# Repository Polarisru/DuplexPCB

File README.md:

# DuplexPCB

This KiCad action plugin tries to create the second part of the duplex PCB.<br>

## Install
Just copy the teardrop folder into the KiCad plugins directory, then restart KiCad. The DuplexPCB plugin should now be available in the Tools/External plugin menu.

## Usage
To duplicate existing PCB you need to create a mapping file first. It must be a simple text file with mapping for all components you want to duplicate.

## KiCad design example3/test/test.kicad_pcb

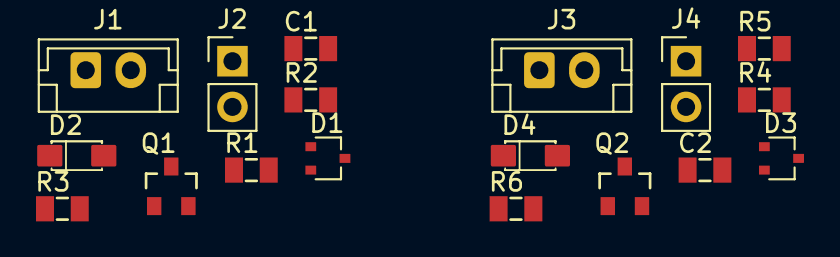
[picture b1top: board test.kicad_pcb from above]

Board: 2 copper layers, 18 parts (0 on the bottom side), 13 nets, no tracks yet.

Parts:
C1, C2: C0805
D1, D3: BAT54SW; SOT-323_SC-70
D2, D4: SMF30A; D_SOD-123FL
J1, J3: Conn_JST_B2B_EH_01x02; JST_EH_B2B-EH-A_1x02_P2.50mm_Vertical
J2, J4: PinHeader_1x02_P2.54mm_Vertical
Q1, Q2: DMN3023L; SOT23-3
R1, R2, R3, R4, R5, R6: R0805

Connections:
GND: C1.2, C2.2, D2.2, D4.2, J1.2, J2.2, J3.2, J4.2, R2.1, R5.1
unnamed: C1.1, D2.1, Q1.1, R3.1
unnamed: C2.1, D4.1, Q2.1, R6.1
unnamed: D1.1, R1.1
unnamed: D1.2, R3.2
unnamed: D1.3, R2.2
unnamed: D3.1, R4.1
unnamed: D3.2, R6.2
unnamed: D3.3, R5.2
unnamed: J1.1, Q1.3, R1.2
unnamed: J2.1, Q1.2
unnamed: J3.1, Q2.3, R4.2
unnamed: J4.1, Q2.2

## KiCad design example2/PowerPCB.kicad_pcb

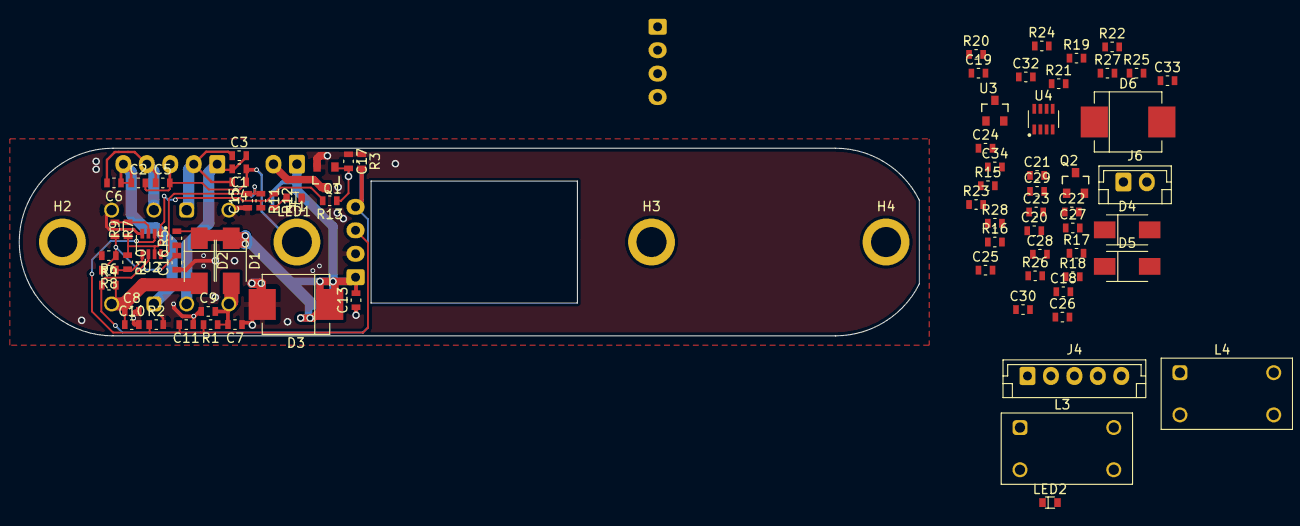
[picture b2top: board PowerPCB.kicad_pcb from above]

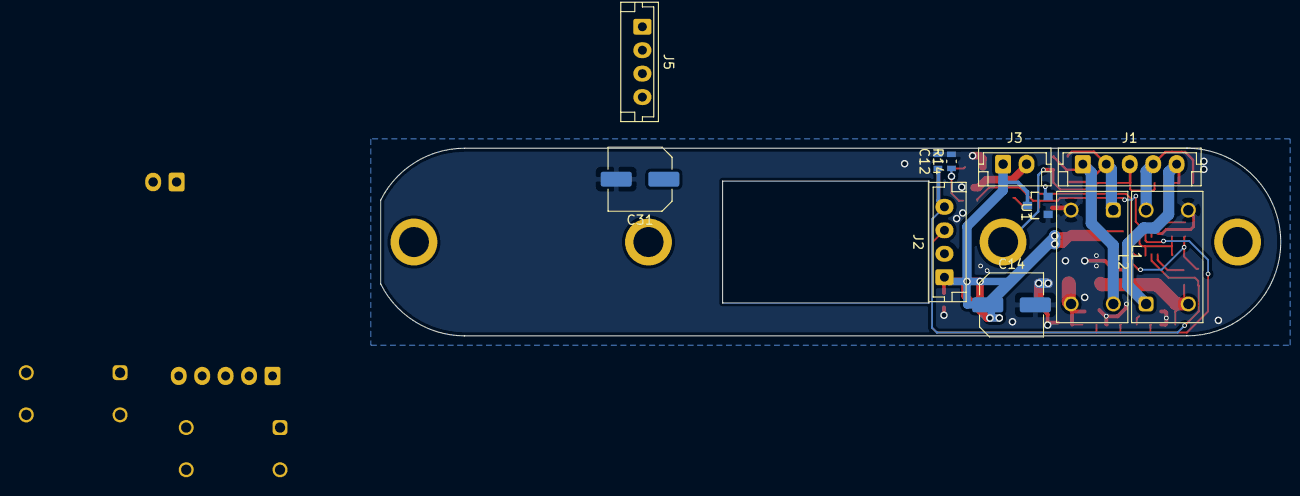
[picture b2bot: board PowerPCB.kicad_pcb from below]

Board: 4 copper layers, 95.9 x 20.0 mm, 90 parts (11 on the bottom side), 37 nets.

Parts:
C1, C2, C4, C5, C9, C10, C18, C19, C21, C22, C26, C27: 100p; C0603
C3, C6, C7, C8, C11, C12, C13, C20, C23, C24, C25, C28, C29, C30: 0.1; C0603
C14, C31: 56uF35V; C_Elec_6.3x5.8
C15, C16, C32, C33: 1.0; C0603
C17, C34: 1n; C0603
D1, D2, D4, D5: VSSAF5L45; D_SMA
D3, D6: 5.0SMDJ28A; D_SMC
H1, H3: Pad; MountingHole_5mm_3.2mm_Pad
H2, H4: Hole; MountingHole_5mm_3.2mm_Pad
J1, J4: POWER; JST_EH_B5B-EH-A_1x05_P2.50mm_Vertical
J2, J5: B4B_EH; JST_EH_B4B-EH-A_1x04_P2.50mm_Vertical
J3, J6: LOAD; JST_EH_B2B-EH-A_1x02_P2.50mm_Vertical
L1, L3: L_WE-7448012501; L_WE_7448012501
L2, L4: L_WE-744877100; L_WE_7448012501
LED1, LED2: 150060RS75020; LED_0603
Q1, Q2: PMV37ENEA; SOT23-3
R1, R4, R5, R15, R18, R19: 75k; R0603
R2, R3, R16, R17: 5k1; R0603
R6, R20: 4k42; R0603
R7, R8, R12, R21, R22, R26: 2k7; R0603
R9, R10, R23, R24: 470k; R0603
R11, R13, R25, R27: 1k; R0603
R14, R28: 15k; R0603
U1, U3: MCP1799T-5002H; SOT23-3
U2, U4: MAX9093AKA; SOT23-8

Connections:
+28V1: C13.2, C14.1, D1.1, D2.1, D3.1, J2.1, J3.1, R5.2, U1.3
+28V2: C30.2, C31.1, D4.1, D5.1, D6.1, J5.1, J6.1, R19.2, U3.3
/VCC5V1: C15.2, R11.1, U1.2, U2.8
/VCC5V2: C32.2, R25.1, U3.2, U4.8
/VOLTP1: C11.2, J2.3, R1.2, R2.1, U2.2
/VOLTP2: C28.2, J5.3, R15.2, R16.1, U4.2
/VOLTS1: C12.1, J2.4, R3.2, R4.1, U2.6
/VOLTS2: C29.1, J5.4, R17.2, R18.1, U4.6
GND: C7.1, C8.2, C9.1, C10.2, C11.1, C12.2, C13.1, C14.2, C15.1, C16.1, C17.1, C24.1, C25.2, C26.1, C27.2, C28.1, C29.2, C30.1, C31.2, C32.1, C33.1, C34.1, D3.2, D6.2, J2.2, J5.2, L1.4, L2.3, L3.4, L4.3, LED1.1, LED2.1, Q1.2, Q2.2, R2.2, R3.1, R6.2, R14.2, R16.2, R17.1, R20.2, R28.2, U1.1, U2.4, U3.1, U4.4
unnamed: C1.1, C2.2, C4.1, C5.2, H1.1, J1.3
unnamed: C1.2, C3.2, J1.1, L1.2
unnamed: C2.1, C6.1, J1.5, L2.1
unnamed: C3.1, C4.2, J1.2, L1.1
unnamed: C5.1, C6.2, J1.4, L2.2
unnamed: C7.2, C9.2, D1.2, L1.3, R1.1
unnamed: C8.1, C10.1, D2.2, L2.4, R4.2
unnamed: C16.2, R5.1, R6.1, R7.2, R8.2
unnamed: C17.2, Q1.1, R13.1, R14.1
unnamed: C18.1, C19.2, C21.1, C22.2, J4.3
unnamed: C18.2, C20.2, H3.1, J4.1, L3.2
unnamed: C19.1, C23.1, J4.5, L4.1
unnamed: C20.1, C21.2, J4.2, L3.1
unnamed: C22.1, C23.2, J4.4, L4.2
unnamed: C24.2, C26.2, D4.2, L3.3, R15.1
unnamed: C25.1, C27.1, D5.2, L4.4, R18.2
unnamed: C33.2, R19.1, R20.1, R21.2, R22.2
unnamed: C34.2, Q2.1, R27.1, R28.1
unnamed: J3.2, Q1.3
unnamed: J6.2, Q2.3
unnamed: LED1.2, R12.2
unnamed: LED2.2, R26.2
unnamed: R7.1, R9.2, U2.3
unnamed: R9.1, R10.1, R11.2, R12.1, R13.2, U2.1, U2.7
unnamed: R8.1, R10.2, U2.5
unnamed: R21.1, R23.2, U4.3
unnamed: R22.1, R24.2, U4.5
unnamed: R23.1, R24.1, R25.2, R26.1, R27.2, U4.1, U4.7

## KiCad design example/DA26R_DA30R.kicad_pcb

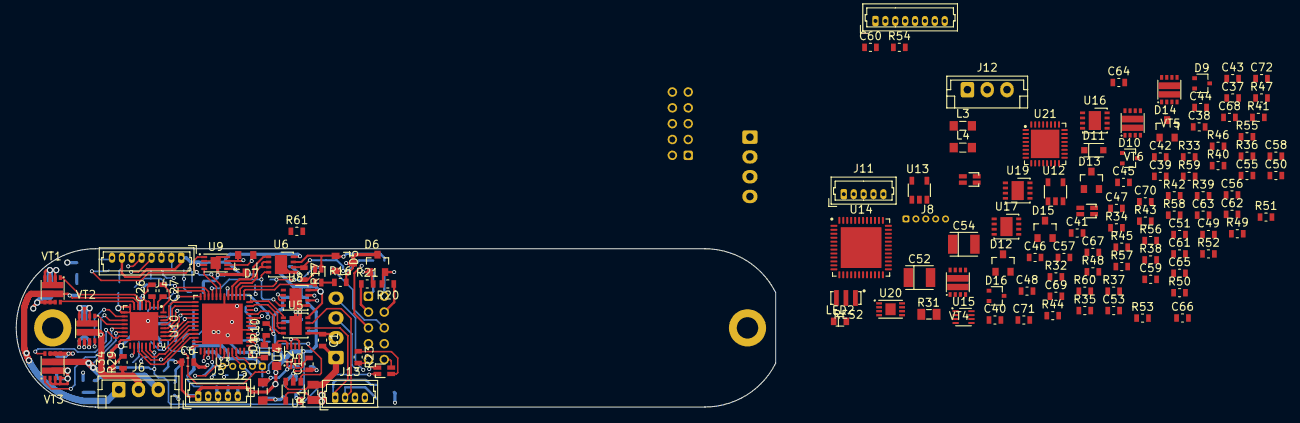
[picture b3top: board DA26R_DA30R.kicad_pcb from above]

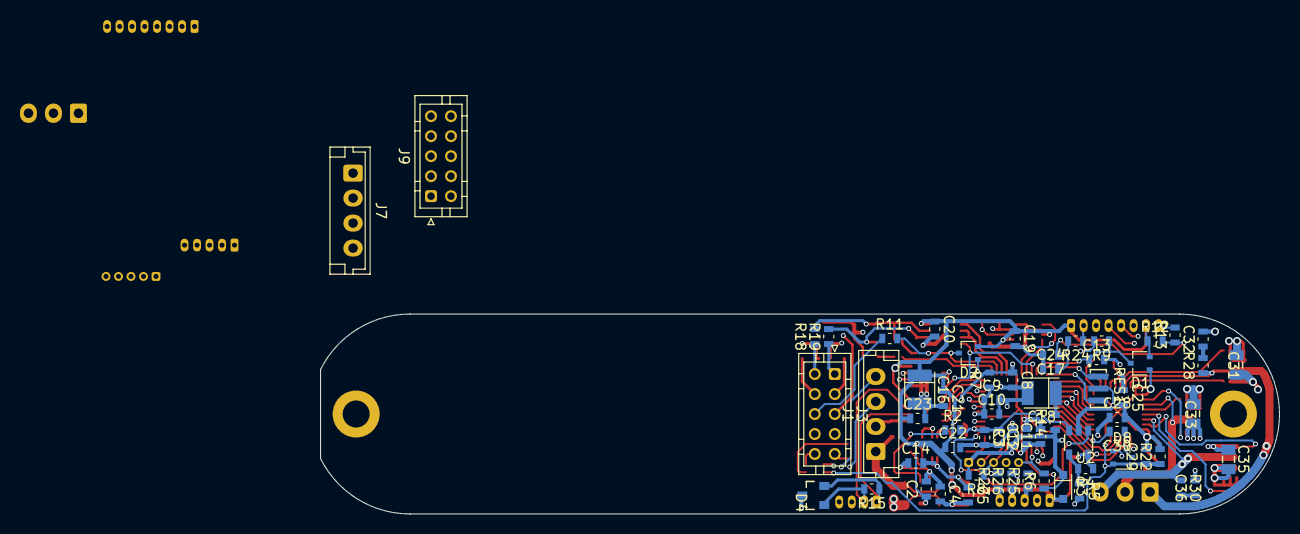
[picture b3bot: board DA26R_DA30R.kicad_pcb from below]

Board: 4 copper layers, 95.9 x 20.0 mm, 198 parts (63 on the bottom side), 179 nets.

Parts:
C1, C7, C9, C11, C14, C15, C24, C26, C28, C29, C30, C37, C43, C45, C47, C50, C51, C60, C62, C64, C65, C66, C67, C69, C71: 1.0; C0603
C2, C3, C6, C8, C10, C12, C13, C17, C19, C20, C21, C22, C23, C25, C27, C38, C39, C42, C44, C46, C48, C49, C53, C55, C56, C57, C58, C59, C61, C63: 0.1; C0603
C4, C5, C40, C41: 10n; C0603
C16, C52: 10.0; CP_Tantal_1311
C18, C54: 330.0; CP_Tantal_1311
C31, C33, C35: 2.2; C0805
C32, C34, C36, C68, C70, C72: 2n7; C0603
D1, D2, D8, D9, D10, D16: BAT854SWF; SOT-323_SC-70
D3, D11: BAT165; D_SOD-323
D4, D5, D6, D12, D13, D14: CDSOT23-T12C; SOT23-3
D7, D15: NUP2105L; SOT23-3
J1, J7: PWR; JST_EH_B4B-EH-A_1x04_P2.50mm_Vertical
J2, J8: SW; Conn_ARM_1x05
J3, J9: INT; JST_PHD_B10B-PHDSS_2x05_P2.00mm_Vertical
J4, J10: Sensor; Molex_PicoBlade_53047-0810_1x08_P1.25mm_Vertical
J5, J11: HALL; Molex_PicoBlade_53047-0510_1x05_P1.25mm_Vertical
J6, J12: Conn_JST_B3B_EH_01x03; JST_EH_B3B-EH-A_1x03_P2.50mm_Vertical
J13: RS485; Molex_PicoBlade_53047-0410_1x04_P1.25mm_Vertical
L1, L3: 10uH; L_0805
L2, L4: 47uH; L_0805
LED1, LED2: LED; LED_0603
R1, R31: 0.01; R0805
R2, R3, R4, R9, R12, R13, R24, R32, R33, R34, R39, R42, R43, R54: 10k; R0603
R5, R15, R17, R35, R45, R47: 120; R0603
R6, R8, R23, R36, R38, R53: 2k7; R0603
R7, R14, R18, R19, R20, R21, R37, R44, R48, R49, R50, R51: 10; R0603
R10, R16, R40, R46: 510; R0603
R11, R25, R26, R27, R41, R55, R56, R57, R61: 1k; R0603
R22, R52: 47k; R0603
R28, R29, R30, R58, R59, R60: 2R2; R0603
RES1, RES2: 16MHz; RES-3
U1, U12: INA194; SOT23-5
U2, U13: MIC6270; SOT23-5
U3, U14: ATSAMC21G18A-MNT; QFN-48-1EP_7x7mm_P0.5mm_EP5.15x5.15mm
U4, U15: MAX15062BATA+T; TDFN-8_2x2mm_P0.5mm
U5, U6, U8, U16, U17, U19: THVD2410DRBR; DFN-8-1EP_3x3mm_P0.65mm_EP1.55x2.4mm
U7, U11, U18, U22: TLP3412; VSON4
U9, U20: MCP2542FDT; DFN-8-1EP_3x2mm_P0.5mm_EP1.3x1.5mm
U10, U21: DRV8320S; QFN-32-1EP_5x5mm_P0.5mm_EP3.6x3.6mm
VT1, VT2, VT3, VT4, VT5, VT6: SiZ250DT; PowerPAIR_3x3

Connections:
+5V2: U19.2, U19.3
/ACE1/+5V: C2.1, C6.1, C16.1, C19.1, C20.1, C21.1, C22.1, C23.1, D1.2, D2.2, D3.2, J4.1, J4.7, J5.1, L2.2, R4.1, R10.2, R12.1, U1.5, U2.5, U4.4, U5.8, U6.8, U8.2, U8.3, U8.8, U9.3, U9.5
/ACE1/+28V: C4.2, C5.2, C25.1, C26.2, C31.2, C33.2, C35.2, L1.1, R1.1, U1.4, U10.3, U10.4, VT1.2, VT1.3, VT1.4, VT1.10, VT2.2, VT2.3, VT2.4, VT2.10, VT3.2, VT3.3, VT3.4, VT3.10
/ACE1/+ARM: C7.1, C8.1, D3.1, J2.1, R6.1, R7.2, R8.2, R14.1, U3.17, U3.36, U3.44
/ACE1/BRAKE: U3.25, U10.30
/ACE1/CANH: D7.2, J3.7, U9.7
/ACE1/CANL: D7.1, J3.8, U9.6
/ACE1/CAN_R: U3.20, U9.4
/ACE1/CAN_T: U3.19, U9.1
/ACE1/CURR: C3.1, R2.2, R3.1, U2.3, U3.3
/ACE1/CURRL: U2.1, U3.2
/ACE1/DCI: C13.1, D1.3, R9.1, U3.22
/ACE1/DCIN: J3.5, R9.2
/ACE1/DCO: D2.3, R11.2, U3.14
/ACE1/DCOUT: J3.6, R11.1
/ACE1/DIR_EXT: U3.15, U6.2, U6.3
/ACE1/DIR_INT: U3.11, U5.2, U5.3
/ACE1/HEART: R61.2, U3.38
/ACE1/H_A: R25.2, U3.29, U10.26
/ACE1/H_B: R26.2, U3.28, U10.27
/ACE1/H_C: R27.2, U3.27, U10.28
/ACE1/INT_A: D4.2, D12.2, J13.1, R15.1, R45.1, U5.6, U16.6
/ACE1/INT_B: D4.1, D12.1, J13.2, R15.2, R45.2, U5.7, U16.7
/ACE1/MEN: C29.1, D8.2, R22.1, U10.22, U11.4
/ACE1/MISO: J4.5, U3.41, U10.18
/ACE1/MOSI: U3.34, U10.19
/ACE1/MOT_DIR: U3.26, U10.29
/ACE1/MOT_EN: C30.2, U3.31
/ACE1/MOT_T: C24.2, R24.2, U3.4
/ACE1/MSCS: J4.6, U3.39
/ACE1/OPTO_A: J3.9, R23.2
/ACE1/OPTO_C: J3.10, U11.2
/ACE1/PHASE_A: J6.1, R28.1, U10.6, VT1.9
/ACE1/PHASE_B: J6.2, R29.1, U10.11, VT2.9
/ACE1/PHASE_C: J6.3, R30.1, U10.14, VT3.9
/ACE1/PWM: U3.30, U10.25
/ACE1/RST: J2.5, R6.2, U3.40
/ACE1/RS_A: J3.1, R19.1
/ACE1/RS_B: J3.2, R18.1
/ACE1/RS_Y: J3.3, R21.1
/ACE1/RS_Z: J3.4, R20.1
/ACE1/RX_EXT: U3.16, U6.1
/ACE1/RX_INT: U3.12, U5.1
/ACE1/SCLK: J4.4, U3.33, U10.20
/ACE1/SCS: U3.32, U10.21
/ACE1/SWC: J2.3, R8.1, U3.45
/ACE1/SWD: J2.2, U3.46
/ACE1/TE: U3.13, U7.1
/ACE1/TX_EXT: U3.21, U6.4, U8.4
/ACE1/TX_INT: U3.9, U5.4
/ACE1/U5V: C17.1, R12.2, R13.1, U3.10
/ACE1/VOLTP: J1.3, U3.7
/ACE1/VOLTS: J1.4, U3.8
/ACE2/+5V: C38.1, C42.1, C52.1, C55.1, C56.1, C57.1, C58.1, C59.1, D9.2, D10.2, D11.2, J10.1, J10.7, J11.1, L4.2, R34.1, R40.2, R42.1, U12.5, U13.5, U15.4, U16.8, U17.8, U19.8, U20.3, U20.5
/ACE2/+28V: C40.2, C41.2, C61.1, C62.2, C67.2, C69.2, C71.2, L3.1, R31.1, U12.4, U21.3, U21.4, VT4.2, VT4.3, VT4.4, VT4.10, VT5.2, VT5.3, VT5.4, VT5.10, VT6.2, VT6.3, VT6.4, VT6.10
/ACE2/+ARM: C43.1, C44.1, D11.1, J8.1, R36.1, R37.2, R38.2, R44.1, U14.17, U14.36, U14.44
/ACE2/BRAKE: U14.25, U21.30
/ACE2/CANH: D15.2, J9.7, U20.7
/ACE2/CANL: D15.1, J9.8, U20.6
/ACE2/CAN_R: U14.20, U20.4
/ACE2/CAN_T: U14.19, U20.1
/ACE2/CURR: C39.1, R32.2, R33.1, U13.3, U14.3
/ACE2/CURRL: U13.1, U14.2
/ACE2/DCI: C49.1, D9.3, R39.1, U14.22
/ACE2/DCIN: J9.5, R39.2
/ACE2/DCO: D10.3, R41.2, U14.14
/ACE2/DCOUT: J9.6, R41.1
/ACE2/DIR_EXT: U14.15, U17.2, U17.3
/ACE2/DIR_INT: U14.11, U16.2, U16.3
/ACE2/HEART: R61.1, U14.38
/ACE2/H_A: R55.2, U14.29, U21.26
/ACE2/H_B: R56.2, U14.28, U21.27
/ACE2/H_C: R57.2, U14.27, U21.28
/ACE2/MEN: C65.1, D16.2, R52.1, U21.22, U22.4
/ACE2/MISO: J10.5, U14.41, U21.18
/ACE2/MOSI: U14.34, U21.19
/ACE2/MOT_DIR: U14.26, U21.29
/ACE2/MOT_EN: C66.2, U14.31
/ACE2/MOT_T: C60.2, R54.2, U14.4
/ACE2/MSCS: J10.6, U14.39
/ACE2/OPTO_A: J9.9, R53.2
/ACE2/OPTO_C: J9.10, U22.2
/ACE2/PHASE_A: J12.1, R58.1, U21.6, VT4.9
/ACE2/PHASE_B: J12.2, R59.1, U21.11, VT5.9
/ACE2/PHASE_C: J12.3, R60.1, U21.14, VT6.9
/ACE2/PWM: U14.30, U21.25
/ACE2/RST: J8.5, R36.2, U14.40
/ACE2/RS_A: J9.1, R49.1
/ACE2/RS_B: J9.2, R48.1
/ACE2/RS_Y: J9.3, R51.1
/ACE2/RS_Z: J9.4, R50.1
/ACE2/RX_EXT: U14.16, U17.1
/ACE2/RX_INT: U14.12, U16.1
/ACE2/SCLK: J10.4, U14.33, U21.20
/ACE2/SWC: J8.3, R38.1, U14.45
/ACE2/SWD: J8.2, U14.46
/ACE2/TE: U14.13, U18.1
/ACE2/TX_EXT: U14.21, U17.4, U19.4
/ACE2/TX_INT: U14.9, U16.4
/ACE2/U5V: C53.1, R42.2, R43.1, U14.10
/ACE2/VOLTP: J7.3, U14.7
/ACE2/VOLTS: J7.4, U14.8
GND: C1.1, C2.2, C3.2, C4.1, C6.2, C7.2, C8.2, C9.2, C10.2, C11.2, C12.2, C13.2, C14.1, C15.1, C16.2, C17.2, C18.2, C19.2, C20.2, C21.2, C22.2, C23.2, C24.1, C25.2, C28.2, C29.2, C31.1, C32.2, C33.1, C34.2, C35.1, C36.2, C37.1, C38.2, C39.2, C40.1, C42.2, C43.2, C44.2, C45.2, C46.2, C47.2, C48.2, C49.2, C50.1, C51.1, C52.2, C53.2, C54.2, C55.2, C56.2, C57.2, C58.2, C59.2, C60.1, C61.2, C64.2, C65.2, C67.1, C68.2, C69.1, C70.2, C71.1, C72.2, D1.1, D2.1, D4.3, D5.3, D6.3, D7.3, D8.1, D9.1, D10.1, D12.3, D13.3, D14.3, D15.3, D16.1, J1.2, J2.4, J4.3, J4.8, J5.2, J7.2, J8.4, J10.3, J10.8, J11.2, J13.3, R3.2, R5.2, R13.2, R16.2, R22.2, R33.2, R35.2, R43.2, R46.2, R52.2, RES1.2, RES2.2, U1.2, U2.2, U3.5, U3.18, U3.35, U3.42, U3.EP, U4.5, U4.7, U5.5, U5.9, U6.5, U6.9, U8.5, U8.9, U9.2, U9.8, U9.EP, U10.8, U10.9, U10.16, U10.23, U10.31, U10.EP, U11.3, U12.2, U13.2, U14.5, U14.18, U14.35, U14.42, U14.EP, U15.5, U15.7, U16.5, U16.9, U17.5, U17.9, U19.5, U19.9, U20.2, U20.8, U20.EP, U21.8, U21.9, U21.16, U21.23, U21.31, U21.EP, U22.3, VT1.5, VT1.6, VT1.7, VT2.5, VT2.6, VT2.7, VT3.5, VT3.6, VT3.7, VT4.5, VT4.6, VT4.7, VT5.5, VT5.6, VT5.7, VT6.5, VT6.6, VT6.7
unnamed: C1.2, J1.1, R1.2, U1.3
unnamed: C9.1, C10.1, R7.1, U3.6
unnamed: C11.1, C12.1, U3.43
unnamed: C5.1, C14.2, L1.2, U4.1, U4.2
unnamed: C15.2, U4.3
unnamed: C18.1, R14.2
unnamed: C26.1, U10.2
unnamed: C27.1, U10.32
unnamed: C27.2, U10.1
unnamed: C28.1, U10.24
unnamed: C30.1, D8.3
unnamed: C32.1, R28.2
unnamed: C34.1, R29.2
unnamed: C36.1, R30.2
unnamed: C37.2, J7.1, R31.2, U12.3
unnamed: C41.1, C50.2, L3.2, U15.1, U15.2
unnamed: C45.1, C46.1, R37.1, U14.6
unnamed: C47.1, C48.1, U14.43
unnamed: C51.2, U15.3
unnamed: C54.1, R44.2
unnamed: C62.1, U21.2
unnamed: C63.1, U21.32
unnamed: C63.2, U21.1
unnamed: C64.1, U21.24
unnamed: C66.1, D16.3
unnamed: C68.1, R58.2
unnamed: C70.1, R59.2
unnamed: C72.1, R60.2
unnamed: D5.1, R18.2, U6.7, U7.3
unnamed: D5.2, R17.1, R19.2, U6.6
unnamed: D6.1, R21.2, U8.6
unnamed: D6.2, R20.2, U8.7
unnamed: D13.1, R48.2, U17.7, U18.3
unnamed: D13.2, R47.1, R49.2, U17.6
unnamed: D14.1, R51.2, U19.6
unnamed: D14.2, R50.2, U19.7
unnamed: J4.2, R24.1
unnamed: J5.3, R25.1
unnamed: J5.4, R26.1
unnamed: J5.5, R27.1
unnamed: J10.2, R54.1
unnamed: J11.3, R55.1
unnamed: J11.4, R56.1
unnamed: J11.5, R57.1
unnamed: L2.1, U4.8
unnamed: L4.1, U15.8
unnamed: LED1.1, U3.1
unnamed: LED1.2, R10.1
unnamed: LED2.1, U14.1
unnamed: LED2.2, R40.1
unnamed: R2.1, U1.1
unnamed: R4.2, R5.1, U2.4
unnamed: R16.1, U7.2
unnamed: R17.2, U7.4
unnamed: R23.1, U11.1
unnamed: R32.1, U12.1
unnamed: R34.2, R35.1, U13.4
unnamed: R46.1, U18.2
unnamed: R47.2, U18.4
unnamed: R53.1, U22.1
unnamed: RES1.1, U3.23
unnamed: RES1.3, U3.24
unnamed: RES2.1, U14.23
unnamed: RES2.3, U14.24
unnamed: U10.5, VT1.1
unnamed: U10.7, VT1.8
unnamed: U10.10, VT2.8
unnamed: U10.12, VT2.1
unnamed: U10.13, VT3.1
unnamed: U10.15, VT3.8
unnamed: U21.5, VT4.1
unnamed: U21.7, VT4.8
unnamed: U21.10, VT5.8
unnamed: U21.12, VT5.1
unnamed: U21.13, VT6.1
unnamed: U21.15, VT6.8

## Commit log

2021-07-20 Moving from single script started
2021-07-21 Try to get simple duplicating to work, not ready yet
2021-07-21 Works now. ToDo: - check errors - add sending parameters - RadioBox doesn't work yet - Add names for sheets to map
2021-07-22 Seems to work so far. ToDo: - improve errors processing - remove re-numeration for the sheets - source code decomposition
2021-07-22 Icon changed, looks not good
2021-07-22 Icon changed
2021-07-23 Rebuilding code to unify regexps, doesn't work yet
2021-07-25 Works so far, have to write more documentation
2021-07-25 Exception added
2021-07-25 Some rubbish added
2022-01-12 Started to positioning references
2022-01-13 Polygons are copied now, references are not Ok yet, must be shifted
2022-01-13 Doesn't work yet, Upright factor must be minded

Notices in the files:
parts and their libraries:
Copyright 2016 Accelerated Designs. All rights reserved.
